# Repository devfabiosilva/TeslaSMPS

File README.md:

# TeslaSMPS

DIY: High Voltage Range Switching Mode Power Supply for Embedded / Solar and industrial systems

## 2026 KiCad Design Contest

Sponsored by PCB Way. See details [here](https://www.pcbway.com/project/shareproject/TeslaSMPS_Simple_3_Transistor_Ultra_Wide_Range_100V_820V_AC_142V_1160V_DC_c3cf9745.html)

### Old handmade version 2015

## Brief description

This is a DIY WVR-SMPS (Wide Voltage Range Switching Mode Power Supply) or simply Tesla SMPS is a wide range and high voltage input for low power embedded systems. This device allows input voltage as low as 100 VAC and as high as 820 VAC in wide frequency range (45 − 450 Hz) or even in DC voltage as low as 142 VDC and as high as 1,160 VDC using only 3 transistors

[State of the art](https://github.com/devfabiosilva/TeslaSMPS/blob/master/01-concept/StateOfTheArt.pdf)

## Basic Block diagram

## PCB Version

You can find PCB version in:

- [Gerber files](https://github.com/devfabiosilva/TeslaSMPS/tree/master/02-schematic_and_gerber_files/gerber)

- [Source code](https://github.com/devfabiosilva/TeslaSMPS/tree/master/03-smd-project)

- [Schematic](https://github.com/devfabiosilva/TeslaSMPS/blob/master/02-schematic_and_gerber_files/2-schematic.pdf)

## Specifications

### Input Voltage:

AC 100 ~ 820 Volts (45 - 450 Hz)

DC 142 ~ 1,160 Volts

### Output Voltage:

DC 25.8 Volts (Insulated)

### Input Power

AC: 46 Va

DC: 34.3 W

### Eficiency

0.78 @ 180 VDC / 127 VAC

0.70 @ 500 VDC / 350 VAC

0.65 @ 1,160 VDC / 820 VAC

### THD
0.75

### Insulation

3,600 Volts

### Inrush current

42.6 Ampères @ 1,160 Volts

### (I^2)s Value

0.38 A^2-seconds

### Primary coil value

1.1 mH

### Primary coil peak current

933 mA

## Features

- Supply for low power Embedded or Solar Systems (max. power 20W)
- Safe high insulation for output voltage (max. 3,600V)
- Limited inrush current 42.6 A @ 1,160 Volts DC (0.38 A^2.s)
- High frequency range in AC operation (45 − 450Hz)
- AC/DC operation
- Static short circuit/overload protection
- Under voltage protection
- Low cost components (only 3 active elements!)
- Startup circuit
- Limited ID (current drain) monitor
- Secondary side grounded for security

## BEFORE YOU BEGIN:

### Remember: SAFETY FIRST

### :skull::skull::skull: DANGER :skull::skull::skull:

This power supply works with very high voltage input. Care MUST be taken to avoid any personal injuries or death

- When power on high voltage, keep clear from input voltage cable.

- For input voltages above 300 Vac/Vdc negative output MUST be grounded with 10 Ohms impedance or less

- Keep in mind that this circuit stores high voltage even when power cord is off. If you want to repair or clear this SMPS wait at least 1 minute after remove power supply cord. Check test points TP1 (Cathode) and TP2 (Anode) pins with Voltimeter in scale 1,000 Vdc after touch or repair this circuit.

- This device has security circuit for under voltage, short circuit and overload. When one of these events occurs, this SMPS will stop working and we need to disconnect power cord, remove the problem and then wait 30 seconds to turn on power cord again. NOTICE: NEVER touch or open this circuit if one of these events occurs EVEN if you disconnected this device from power cord.

## Building the transformer using recycled materials

You will need to rewind the transformer following these steps

## Step 1

- Find an old ATX power PCB

## Step 2

- Disassemble the transformer core

You can use a EI or EE type ferrite core

[reference 1](https://en.wikipedia.org/wiki/Ferrite_core)

[reference 2](https://www.mag-inc.com/Products/Ferrite-Cores/Ferrite-Shapes/Learn-More-about-Ferrite-Shapes)

## Step 3

- Take the spool out of the core

## Step 4

- Rewind the transformer spool

- Rewinding turns:

- **A** - 4 turns (Secondary coil) (5 x 0.1 mm diameter *)

- **B** - 30 turns (Primary coil) (3 x 0.05 mm diameter *)

- **C** - 5 turns (Positive feedback coil) (0.1 mm diameter)

- **D** - 4 turns (Control circuit supply) (0.1 mm diameter)

_* Primary and secondary coil [skin effect](https://en.wikipedia.org/wiki/Skin_effect). Just interlace 3 x 0.05 mm copper wires and rewind the primary transformer spool and 5 x 0.1 mm copper wires in secondary coil_

See example below:

_4 x 0.1mm interlaced wire_

## LAYERS AND INSULATORS

### INSULATION (WARNING !!!)

It is EXTREMELY IMPORTANT to insulate high voltage from secundary side. To do this you will need 6 layers of insulating tape to insulate 3.6 kV. Thus:

Transformer spool cross section example:

Primary coil winding

_Control circuit supply_ and _control circuit supply_

Finishing insulation

### Creating the core gap:

[Flyback topology](https://www.coilcraft.com/en-us/edu/series/a-guide-to-flyback-transformers/) needs a [core gap](https://www.e-magnetica.pl/doku.php/air_gap) due to high peek flux to avoid saturation of the [ferrite coil](https://resources.pcb.cadence.com/blog/2022-what-is-a-ferrite-core)

So we need to create one _approx. 120um_ core gap using a non magnetic material. E.g.: a piece of paper

Take a A4 paper

Cut a piece of paper

Fix the piece of paper in transforme core

Close the transformer core

Finally your transformer is ready to work in your Tesla SMPS

## Contact

Feel free to contact me at [fabioegel@gmail.com](mailto:fabioegel@gmail.com)

## Sponsors

This project is sponsored by [PCBWay](https://www.pcbway.com/)

## References

- [AN4148 Audible Noise Reduction Techniques for FPS Applications](https://www.onsemi.com/download/application-notes/pdf/an-4148.pdf)
- [High Voltage Printed Circuit Design & Manufactoring Notebook](https://www.magazines007.com/pdf/High-Voltage-PCDesign.pdf)
- [EEVblog #678 - What is a PCB Spark Gap?](https://www.youtube.com/watch?v=vfP_65gSSBU)

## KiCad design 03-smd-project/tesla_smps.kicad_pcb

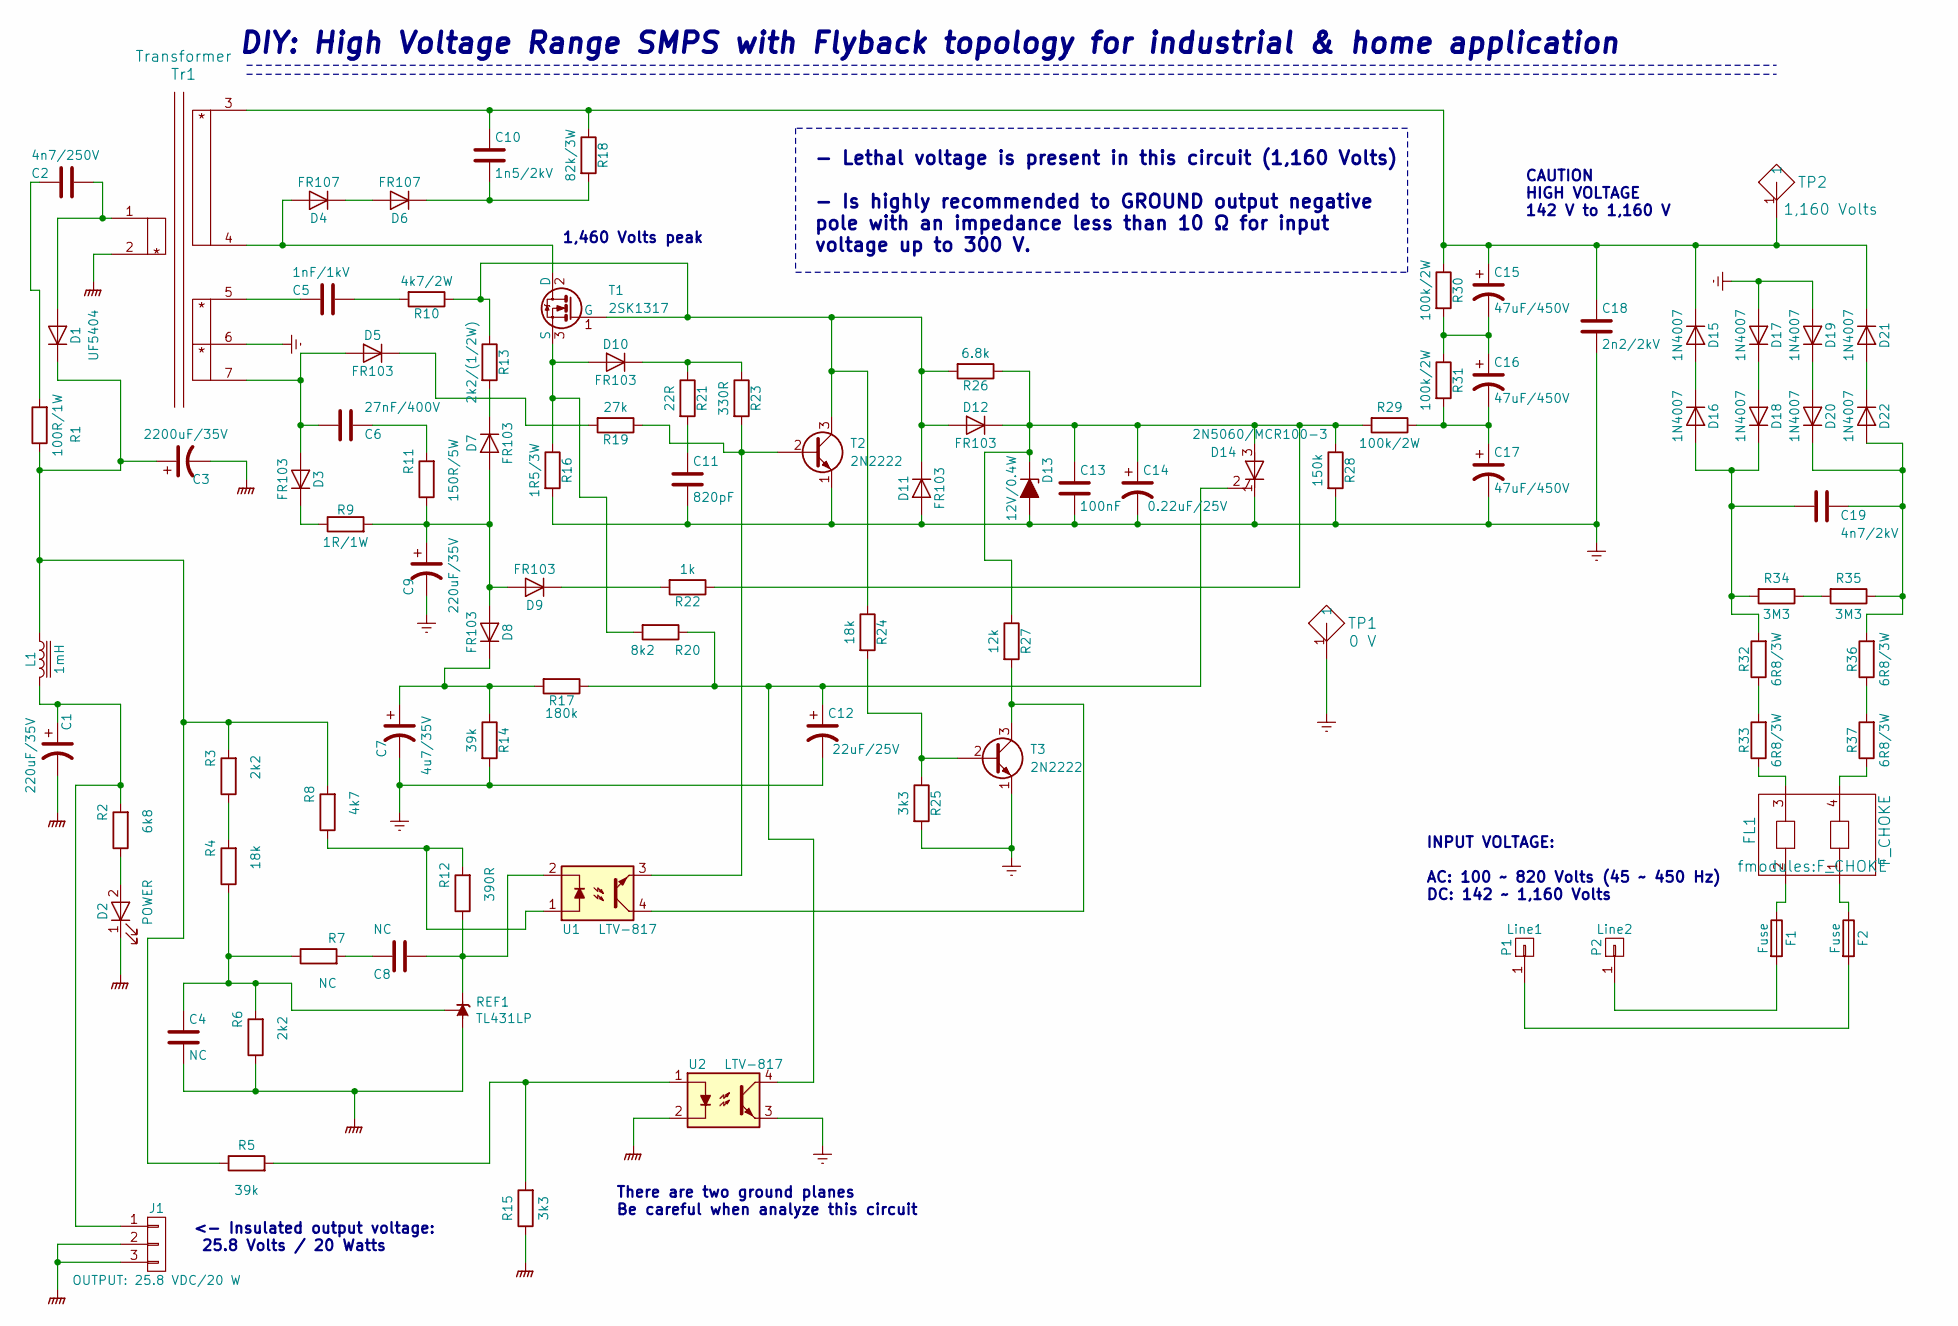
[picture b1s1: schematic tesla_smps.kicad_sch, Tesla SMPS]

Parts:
C1, C9: 220uF/35V; CP_Radial_D8.0mm_P3.50mm
C2: 4n7/250V; C_Disc_D10.0mm_W2.5mm_P5.00mm
C3: 2200uF/35V; CP_Radial_D16.0mm_P7.50mm
C4, C8: NC; C_Disc_D3.4mm_W2.1mm_P2.50mm
C5: 1nF/1kV; C_Disc_D10.0mm_W2.5mm_P5.00mm
C6: 27nF/400V; C_Disc_D7.5mm_W4.4mm_P5.00mm
C7: 4u7/35V; CP_Radial_D5.0mm_P2.50mm
C10: 1n5/2kV; C_Disc_D10.0mm_W2.5mm_P5.00mm
C11: 820pF; C_Disc_D3.4mm_W2.1mm_P2.50mm
C12: 22uF/25V; CP_Radial_D5.0mm_P2.50mm
C13: 100nF; C_Disc_D3.4mm_W2.1mm_P2.50mm
C14: 0.22uF/25V; CP_Radial_D4.0mm_P2.00mm
C15, C16, C17: 47uF/450V; CP_Radial_D16.0mm_P7.50mm
C18: 2n2/2kV; C_Disc_D7.5mm_W4.4mm_P5.00mm
C19: 4n7/2kV; C_Disc_D7.5mm_W4.4mm_P5.00mm
D1: UF5404; D_DO-201AD_P5.08mm_Vertical_AnodeUp
D2: POWER; LED_D5.0mm
D3, D5, D7, D8, D9, D10, D11, D12: FR103; D_SMA_Handsoldering
D4, D6: FR107; D_SMA_Handsoldering
D13: 12V/0.4W; D_SOD-323F
D14: 2N5060/MCR100-3; TO-92
D15, D16, D17, D18, D19, D20, D21, D22: 1N4007; D_SMA
F1, F2: Fuse; Fuse_Bourns_MF-RHT1000
FL1: F_CHOKE
J1: OUTPUT: 25.8 VDC/20 W; FanPinHeader_1x03_P2.54mm_Vertical
L1: 1mH; L_Toroid_Vertical_L13.0mm_W6.5mm_P5.60mm
P1: Line1; F_PIN
P2: Line2; F_PIN
R1: 100R/1W; R_Axial_DIN0414_L11.9mm_D4.5mm_P5.08mm_Vertical
R2: 6k8; R_0805_2012Metric
R3, R6: 2k2; R_0402_1005Metric
R4, R24: 18k; R_0402_1005Metric
R5, R14: 39k; R_0402_1005Metric
R7: NC; R_0402_1005Metric
R8: 4k7; R_0805_2012Metric
R9: 1R/1W; R_Axial_DIN0414_L11.9mm_D4.5mm_P5.08mm_Vertical
R10: 4k7/2W; R_Axial_DIN0617_L17.0mm_D6.0mm_P5.08mm_Vertical
R11: 150R/5W; R_Axial_DIN0617_L17.0mm_D6.0mm_P7.62mm_Vertical
R12: 390R; R_0402_1005Metric
R13: 2k2/(1/2W); R_Axial_DIN0309_L9.0mm_D3.2mm_P2.54mm_Vertical
R15, R25: 3k3; R_0402_1005Metric
R16: 1R5/3W; R_Axial_DIN0614_L14.3mm_D5.7mm_P5.08mm_Vertical
R17: 180k; R_0402_1005Metric
R18: 82k/3W; R_Axial_DIN0516_L15.5mm_D5.0mm_P7.62mm_Vertical
R19: 27k; R_0402_1005Metric
R20: 8k2; R_0402_1005Metric
R21: 22R; R_0402_1005Metric
R22: 1k; R_2010_5025Metric_Pad1.40x2.65mm_HandSolder
R23: 330R; R_0402_1005Metric
R26: 6.8k; R_0402_1005Metric
R27: 12k; R_0402_1005Metric
R28: 150k; R_0402_1005Metric
R29, R30, R31: 100k/2W; R_Axial_DIN0516_L15.5mm_D5.0mm_P7.62mm_Vertical
R32, R33, R36, R37: 6R8/3W; R_Axial_DIN0516_L15.5mm_D5.0mm_P7.62mm_Vertical
R34, R35: 3M3; R_Axial_DIN0411_L9.9mm_D3.6mm_P7.62mm_Vertical
REF1: TL431LP; TO-92_Inline
T1: 2SK1317; TO-3P-3_Vertical
T2, T3: 2N2222; TO-92
TP1: 0 V; 1pin
TP2: 1,160 Volts; 1pin
Tr1: Transformer; F_TR
U1, U2: LTV-817; DIP-4_W7.62mm_LongPads

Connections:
GNDPWR: C1.2, C3.2, C4.2, D2.1 (K), J1.2, J1.3, R6.1, R15.1, REF1.2 (A), Tr1.2, U2.2
GNDREF: C7.2, C9.2, C11.2, C12.2, C13.2, C14.2, C17.2, C18.2, D11.2 (A), D13.2 (A), D14.1 (K), D17.2 (A), D19.2 (A), R14.2, R16.2, R25.2, R28.2, T2.1 (E), T3.1 (E), TP1.1, Tr1.6, U2.3
unnamed: C1.1, J1.1, L1.2, R2.2
unnamed: C2.1, D1.2 (A), Tr1.1
unnamed: C2.2, R1.2
unnamed: C3.1, D1.1 (K), L1.1, R1.1, R3.2, R5.1, R8.2
unnamed: C4.1, R4.1, R6.2, R7.1, REF1.1 (REF)
unnamed: C5.1, R10.2
unnamed: C5.2, Tr1.5
unnamed: C6.1, R11.2
unnamed: C6.2, D3.2 (A), D5.2 (A), Tr1.7
unnamed: C7.1, D8.1 (K), R14.1, R17.2
unnamed: C8.1, R12.1, REF1.3 (K), U1.2
unnamed: C8.2, R7.2
unnamed: C9.1, D7.2 (A), D8.2 (A), D9.2 (A), R9.2, R11.1
unnamed: C10.1, C15.1, C18.1, D15.1 (K), D21.1 (K), R18.1, R30.1, TP2.1, Tr1.3
unnamed: C10.2, D6.1 (K), R18.2
unnamed: C11.1, R21.2
unnamed: C12.1, D14.2 (G), R17.1, R20.1, U2.4
unnamed: C13.1, C14.1, D12.1 (K), D13.1 (K), D14.3 (A), R22.1, R26.1, R27.1, R28.1, R29.2
unnamed: C15.2, C16.1, R30.2, R31.1
unnamed: C16.2, C17.1, R29.1, R31.2
unnamed: C19.1, D20.1 (K), D22.2 (A), R35.1, R36.2
unnamed: C19.2, D16.2 (A), D18.1 (K), R32.2, R34.2
unnamed: D2.2 (A), R2.1
unnamed: D3.1 (K), R9.1
unnamed: D4.1 (K), D6.2 (A)
unnamed: D4.2 (A), T1.2 (D), Tr1.4
unnamed: D5.1 (K), R19.2
unnamed: D7.1 (K), R13.2
unnamed: D9.1 (K), R22.2
unnamed: D10.1 (K), R21.1, R23.1
unnamed: D10.2 (A), R16.1, R20.2, T1.3 (S)
unnamed: D11.1 (K), D12.2 (A), R10.1, R13.1, R24.1, R26.2, T1.1 (G), T2.3 (C)
unnamed: D15.2 (A), D16.1 (K)
unnamed: D17.1 (K), D18.2 (A)
unnamed: D19.1 (K), D20.2 (A)
unnamed: D21.2 (A), D22.1 (K)
unnamed: F1.1, FL1.2
unnamed: F1.2, P2.1
unnamed: F2.1, FL1.1
unnamed: F2.2, P1.1
unnamed: FL1.3, R33.1
unnamed: FL1.4, R37.1
unnamed: R3.1, R4.2
unnamed: R8.1, R12.2, U1.1
unnamed: R5.2, R15.2, U2.1
unnamed: R19.1, R23.2, T2.2 (B), U1.3
unnamed: R24.2, R25.1, T3.2 (B)
unnamed: R27.2, T3.3 (C), U1.4
unnamed: R32.1, R33.2
unnamed: R34.1, R35.2
unnamed: R36.1, R37.2

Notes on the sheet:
- Lethal voltage is present in this circuit (1,160 Volts) - Is highly recommended to GROUND output negative pole with an impedance less than 10 Ω for input voltage up to 300 V.
INPUT VOLTAGE: AC: 100 ~ 820 Volts (45 ~ 450 Hz) DC: 142 ~ 1,160 Volts
1,460 Volts peak
<- Insulated output voltage: 25.8 Volts / 20 Watts
CAUTION HIGH VOLTAGE 142 V to 1,160 V
DIY: High Voltage Range SMPS with Flyback topology for industrial & home application
There are two ground planes Be careful when analyze this circuit

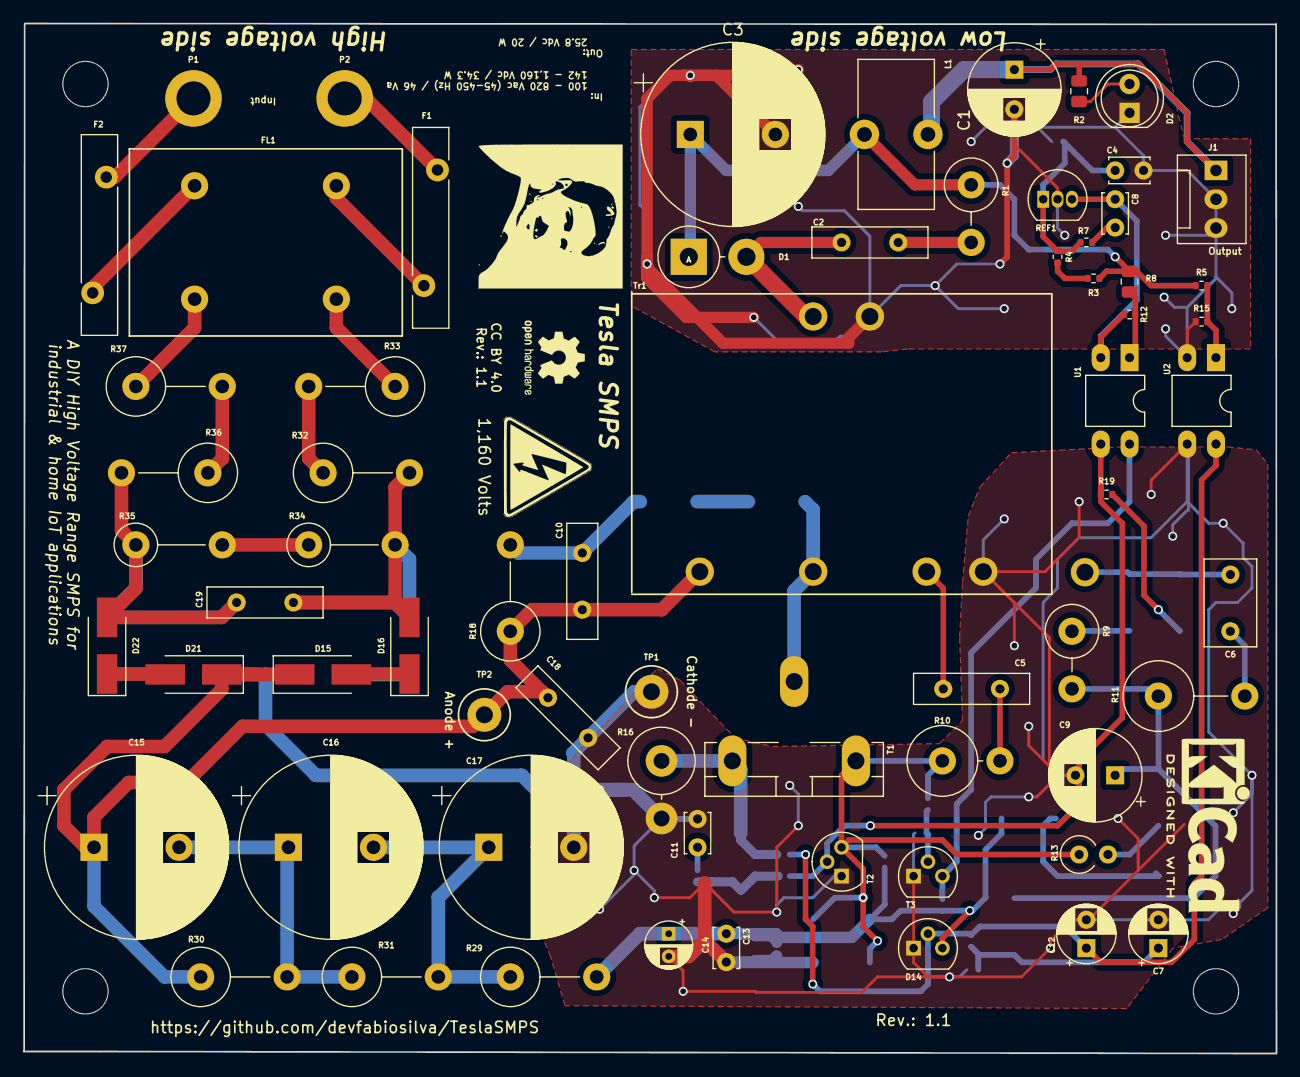
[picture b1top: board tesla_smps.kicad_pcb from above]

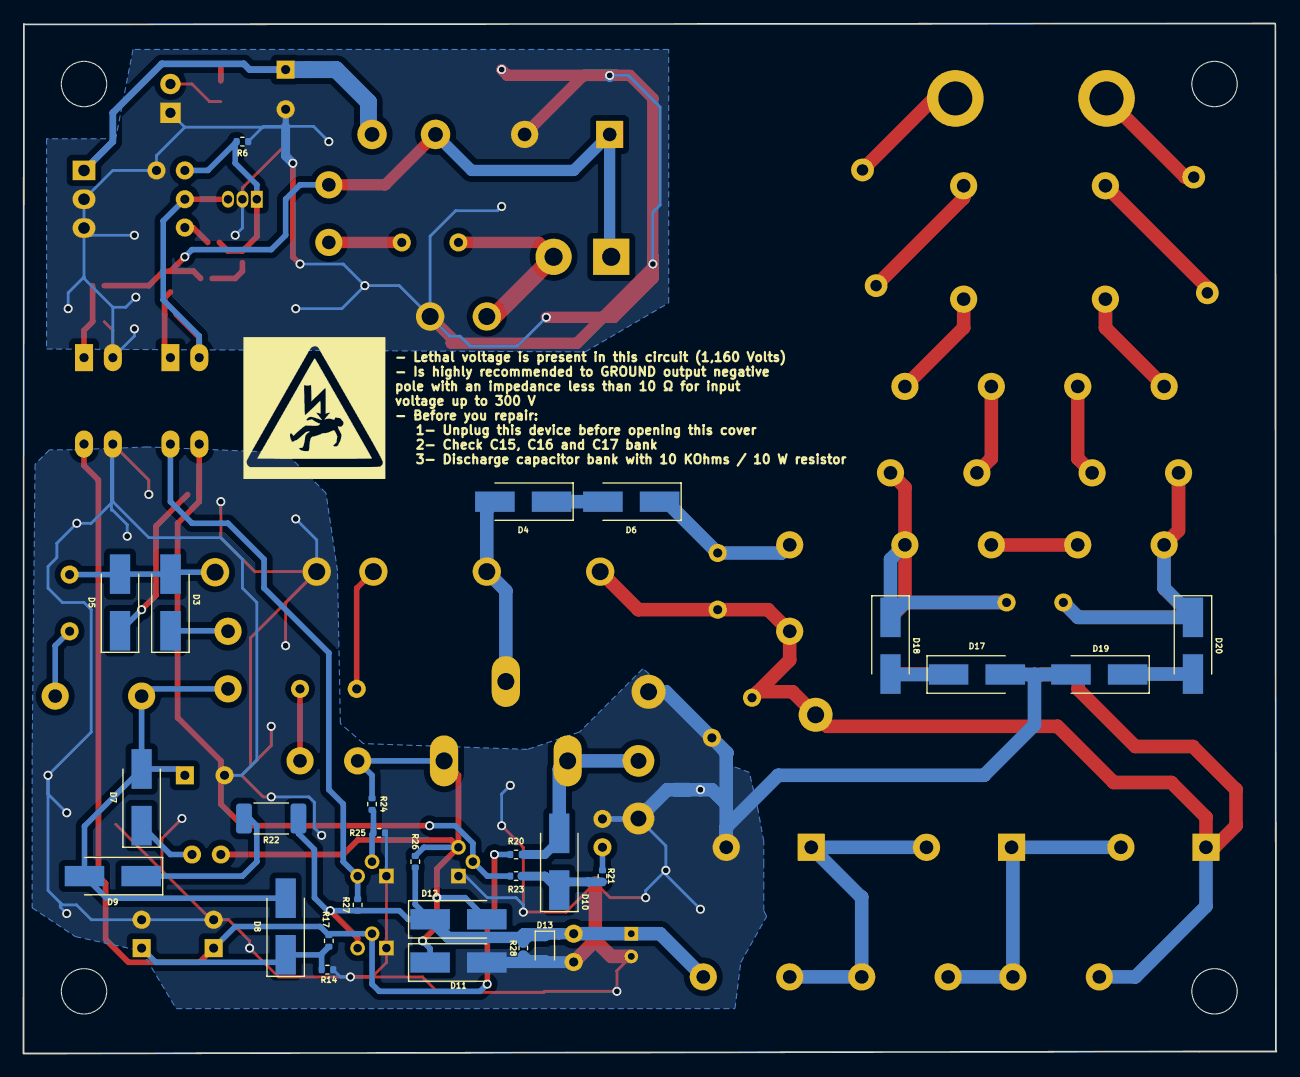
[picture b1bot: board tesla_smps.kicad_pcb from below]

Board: 2 copper layers, 110.5 x 90.8 mm, 94 parts (27 on the bottom side), 53 nets.

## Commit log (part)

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2024-06-08 Update LICENSE
2024-06-08 Updating README.md
2024-06-08 Reorder topics
2024-06-09 Add Build the transformer tutorial
2024-06-09 Correcting misc file extension in README.md
2024-06-10 Add rewinding coils tutorial
2024-06-10 Add coil numbers
2024-06-30 Working on documentation
2024-06-30 Resizing images
2024-06-30 Add important information for DANGER topic
2024-06-30 Add 'creating core gap' topic in documentation
2024-06-30 Change ferrite core reference
2024-07-01 Add 'sponsor', 'contact' and 'references'
2024-07-14 Update to Kicad 8
2024-07-15 Add PCB layout example
2024-07-17 Resizing imgs
2024-08-05 Add new PCB version and changelogs
2025-03-29 Add release candidate for PCB version 1.1
2025-04-27 Testing ChatGPT documentation suggestion template

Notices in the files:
03-smd-project/tesla_smps.kicad_pcb:
Copyright: CC BY 4.0
https://creativecommons.org/licenses/by/4.0
CC BY 4.0
